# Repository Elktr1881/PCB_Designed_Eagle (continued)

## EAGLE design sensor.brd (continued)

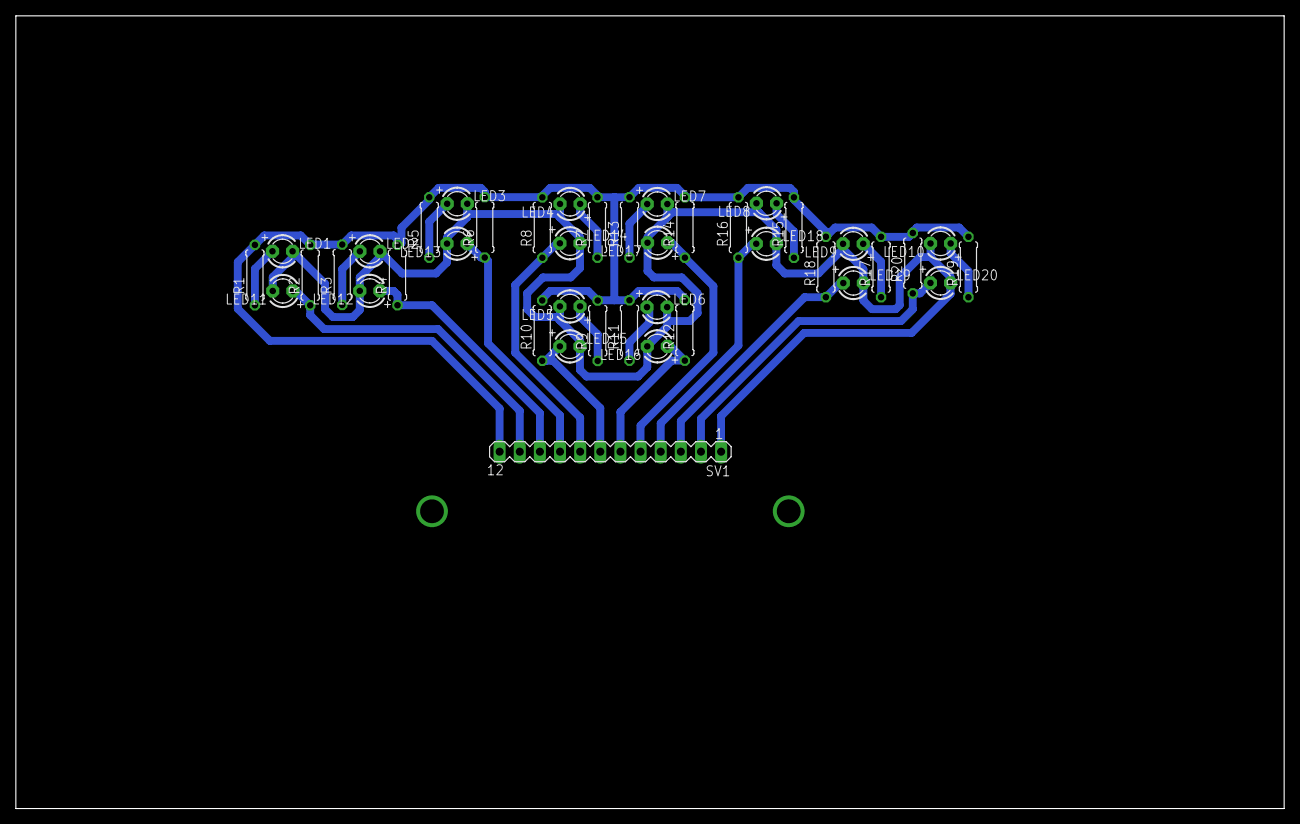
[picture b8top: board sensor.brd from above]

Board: 2 copper layers, 160.0 x 100.0 mm, 41 parts (0 on the bottom side), 22 nets.
